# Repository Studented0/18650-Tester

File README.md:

# CellScan
 
A 4-channel 18650 battery analyzer. Tests up to 4 cells at once and measures voltage, capacity in mAh, and internal resistance per channel. Results show on a small OLED with a rotary encoder to navigate, and a WiFi dashboard to start and stop tests remotely/edit settings.
 
---
 
## Screenshots

---
 
## Why I built this
 
My science fair project was a 3S34P battery pack from 34 salvaged 18650 cells. I bought a cheap tester off Amazon to sort them but I wanted to know how it actually worked. I also wanted an excuse to learn PCB design. CellScan is the result, a two-layer PCB with SMD assembly through JLCPCB.
 
---
 
## Hardware
 
Two-layer board, 100×150mm, designed in KiCad 9. SMD components assembled by JLCPCB. Through-hole parts soldered by hand after the board arrives: four MOSFETs, four cement resistors, four cell holders, the OLED header, the ESP32 dev board, and the rotary encoder. The cement resistors run hot under load so they sit raised slightly off the board.
 
Each channel has an INA219 current sensor, an IRLZ44N MOSFET as a discharge switch, and a 1Ω 10W cement resistor as the load. All four INA219s share an I2C bus through a TCA9548A multiplexer since they would otherwise have the same address. Each channel also has a TP4056 lithium charger for charging and discharging. 
 
---
 
## How it measures
 
**Voltage** — INA219 reads bus voltage continuously on each channel.
 
**Capacity** — ESP32 switches the MOSFET on to start discharge. Capacity accumulates by coulomb counting every 500ms until the cell hits the cutoff voltage.
 
`mAh += current_mA * (elapsed_ms / 3600000.0)`
 
**Internal resistance (DCIR)** — Measured at test start using voltage sag. MOSFET off, read open-circuit voltage. MOSFET on, wait 100ms, read loaded voltage and current.
 
`ESR (mΩ) = (V_oc - V_load) / I_load * 1000`
 
---
 
## Rotary Encoder
 
EC11 encoder wired directly to the ESP32. Rotate to switch between channels, press to open a menu, long press to go back. From the menu you can start a test, stop it, or adjust the cutoff voltage per channel. 
 
### Wiring
 
| Signal | GPIO |
|--------|------|
| ENC_A | 15 |
| ENC_B | 2 |
| ENC_SW | 5 |
| SDA | 21 |
| SCL | 22 |
 
---
 
## Firmware
 
`firmware/CellScan.ino` — state machine per channel, coulomb counting, DCIR measurement, TP4056 CE control, rotary encoder UI, OLED display, WiFi dashboard.
 
Libraries needed: Adafruit INA219, Adafruit SSD1306, Adafruit GFX, ArduinoJson. Install through Arduino IDE library manager. Board: ESP32 Dev Module.
 
---
 
## Bill of Materials
 
SMD parts ordered through JLCPCB assembly. Through-hole parts sourced separately.
 
| Component | Qty | LCSC | Note |
|-----------|-----|------|------|
| 100nF 0402 cap | 11 | C1525 | Basic |
| 10kΩ 0402 resistor | 7 | C25744 | Basic |
| 5.1kΩ 0402 resistor | 2 | C25905 | Basic — USB-C CC pull-downs |
| 1.2kΩ 0402 resistor | 4 | C25862 | Extended — TP4056 PROG |
| 1kΩ 0402 resistor | 8 | C11702 | Basic — LED series |
| Red LED 0402 | 8 | C71911 | Extended |
| INA219AIDR | 4 | C138706 | Extended |
| TCA9548AMRGER | 1 | C2876717 | Extended |
| TP4056 SOP-8 | 4 | C16581 | Extended |
| GCT USB4125 USB-C | 1 | C2682777 | Extended |
 
| Component | Qty | Link |
|-----------|-----|------|
| ESP32 WROOM-32 dev board | 1 | [Amazon](https://www.amazon.com/dp/B08D5ZD528) |
| IRLZ44N MOSFET | 4 | [Amazon](https://www.amazon.com/Technologies-Threshold-Protective-Packaging-IRLZ44NPBF/dp/B0FMQCYG6Q/) |
| 1Ω 10W cement resistor | 4 | [Amazon](https://www.amazon.com/Resistors-Wirewound-Resistance-Precharge-Horizontal/dp/B09V5MTX8Q/) |
| 18650 cell holders | 4 | [Amazon](https://www.amazon.com/Battery-Storage-Holder-Button-Single/dp/B07KD9JLH3/) |
| SSD1306 OLED 0.96" | 1 | [Amazon](https://www.amazon.com/UCTRONICS-SSD1306-Self-Luminous-Display-Raspberry/dp/B072Q2X2LL/) |
| EC11 rotary encoder | 1 | already owned |
 
---
 
## Repository Structure
 
```
18650-Tester/
├── BOM.csv
├── README.md
├── firmware/
│   └── CellScan.ino
└── hardware/
    ├── CellScan_Schematic.kicad_sch
    ├── CellScan_Schematic.kicad_pcb
    ├── CellScan_Schematic.kicad_pro
    ├── CellScan_Schematic.pdf
    ├── libraries/
    │   └── ESP32-DevKitC-30PIN.kicad_mod
    └── gerbers/
```
 
---
 
## License
 
[MIT](LICENSE)

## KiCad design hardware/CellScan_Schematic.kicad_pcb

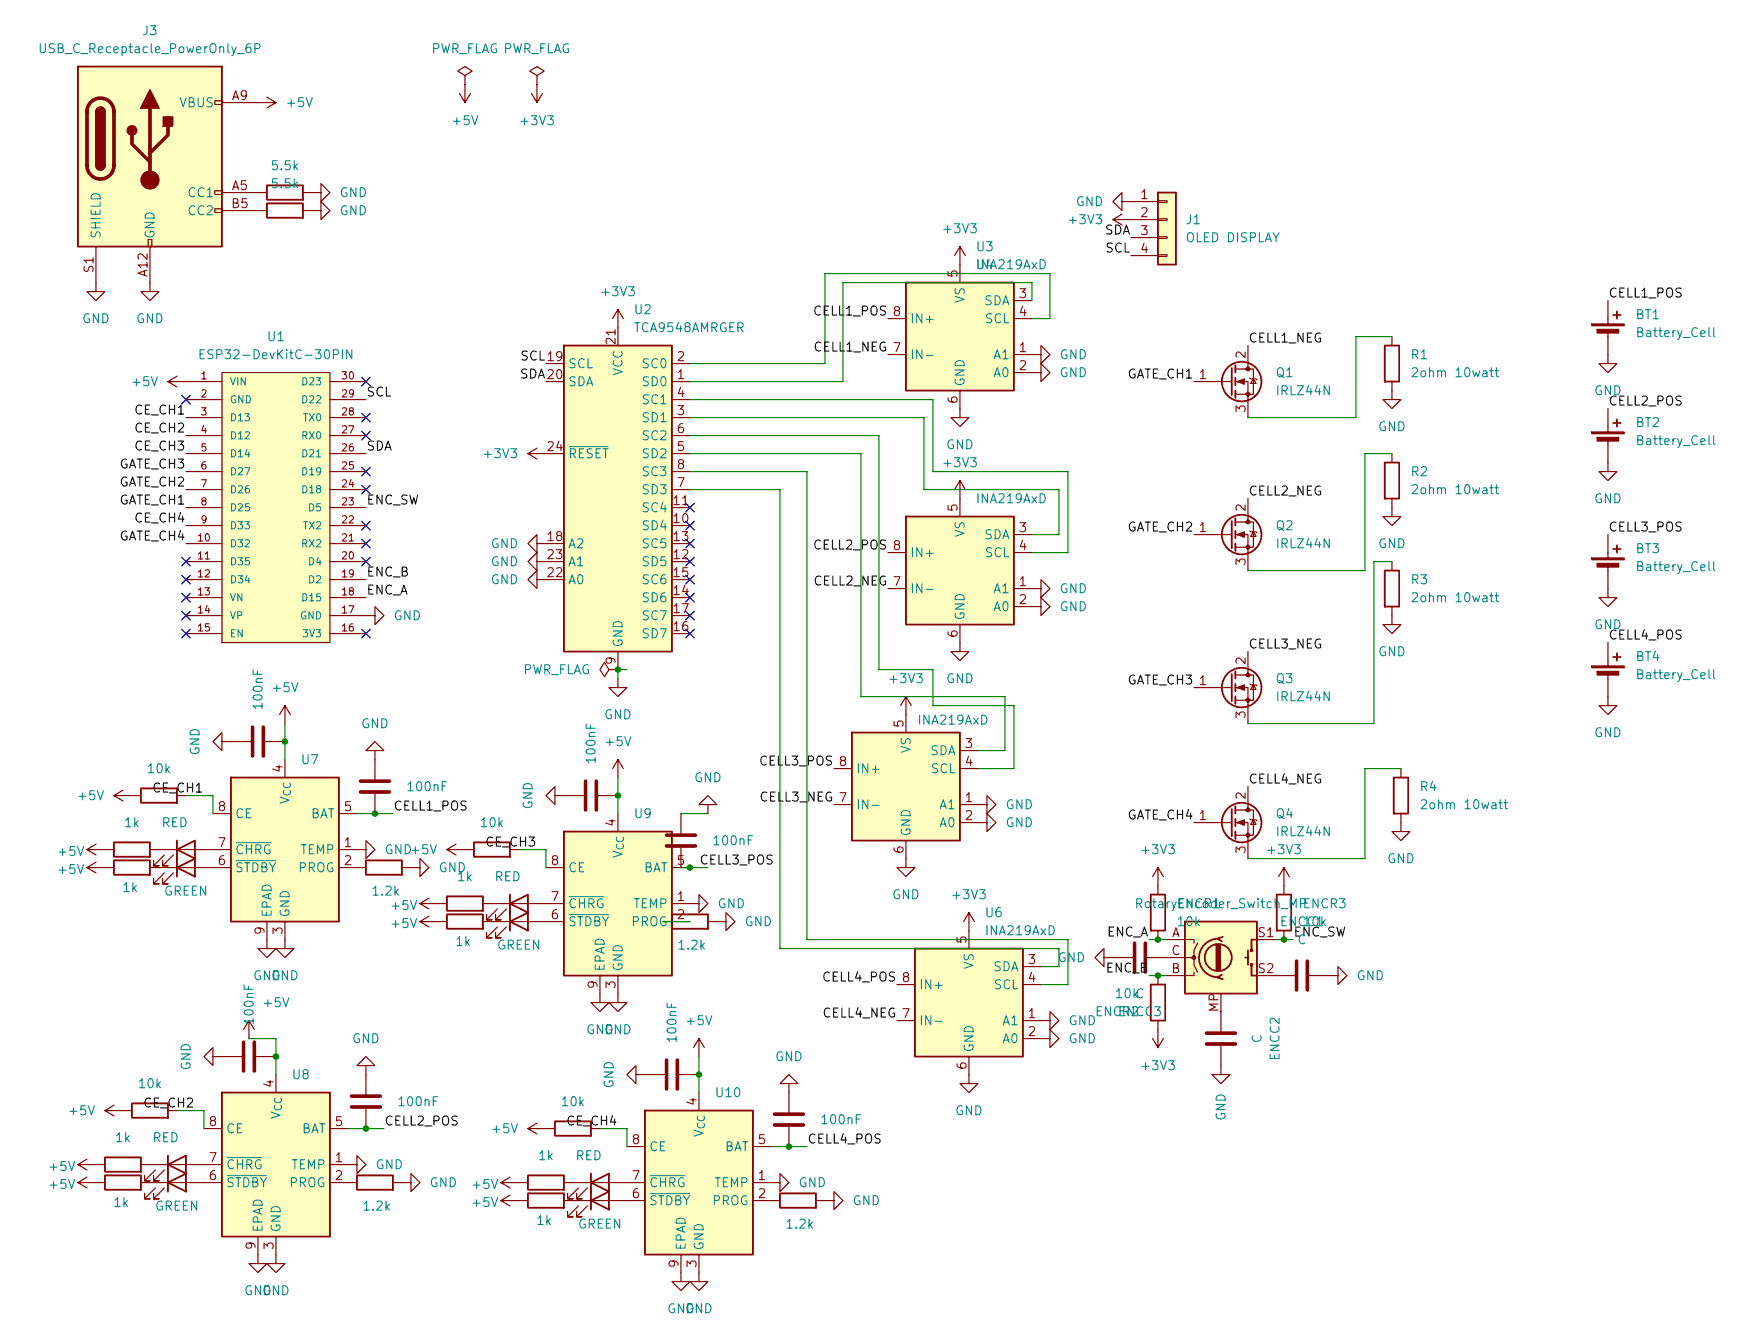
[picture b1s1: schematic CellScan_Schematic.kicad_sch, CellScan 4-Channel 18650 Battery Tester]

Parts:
BAT1.1, BAT2.1, BAT3.1, BAT4.1: 10k; R_0402_1005Metric
BAT1.2, BAT2.2, BAT3.2, BAT4.2: 1.2k; R_0402_1005Metric
BAT1.3, BAT1.4, BAT2.3, BAT2.4, BAT3.3, BAT3.4, BAT4.3, BAT4.4: 100nF; C_0402_1005Metric
BAT1GREEN1, BAT1RED1, BAT2GREEN1, BAT2RED1, BAT3GREEN1, BAT3RED1, BAT4GREEN1, BAT4RED1: 1k; LED_0402_1005Metric
BT1, BT2, BT3, BT4: Battery_Cell; BatteryHolder_Keystone_1042_1x18650
ENCC1, ENCC2, ENCC3: C; C_0402_1005Metric
ENCR1, ENCR2, ENCR3: 10k; R_0402_1005Metric
GREEN1, GREEN2, GREEN3, GREEN4: GREEN; LED_0402_1005Metric
J1: OLED DISPLAY; PinHeader_1x04_P2.54mm_Vertical
J3: USB_C_Receptacle_PowerOnly_6P; USB_C_Receptacle_GCT_USB4125-xx-x-0190_6P_TopMnt_Horizontal
Q1, Q2, Q3, Q4: IRLZ44N; TO-220-3_Vertical
R1, R2, R3, R4: 2ohm 10watt; R_Axial_Power_L48.0mm_W12.5mm_P55.88mm
R5, R6: 5.5k; R_0402_1005Metric
RED1, RED2, RED3, RED4: RED; LED_0402_1005Metric
SW1: RotaryEncoder_Switch_MP; RotaryEncoder_Alps_EC11E-Switch_Vertical_H20mm
U1: ESP32-DevKitC-30PIN
U2: TCA9548AMRGER; Texas_RGE0024C_VQFN-24-1EP_4x4mm_P0.5mm_EP2.1x2.1mm
U3, U4, U5, U6: INA219AxD; SOIC-8_3.9x4.9mm_P1.27mm
U7, U8, U9, U10: TP4056-42-ESOP8; SOIC-8-1EP_3.9x4.9mm_P1.27mm_EP2.41x3.3mm_ThermalVias

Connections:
+3V3: ENCR1.1, ENCR2.1, ENCR3.1, J1.2, U2.21 (VCC), U2.24 (~RESET), U3.5 (VS), U4.5 (VS), U5.5 (VS), U6.5 (VS)
+5V: BAT1.1.1, BAT1.4.2, BAT1GREEN1.1, BAT1RED1.1, BAT2.1.1, BAT2.4.2, BAT2GREEN1.1, BAT2RED1.1, BAT3.1.1, BAT3.4.2, BAT3GREEN1.1, BAT3RED1.1, BAT4.1.1, BAT4.4.2, BAT4GREEN1.1, BAT4RED1.1, J3.A9 (VBUS), J3.B9 (VBUS), U1.1 (VIN), U7.4 (V_{CC}), U8.4 (V_{CC}), U9.4 (V_{CC}), U10.4 (V_{CC})
/CELL1_NEG: Q1.2 (D), U3.7 (IN-)
/CELL1_POS: BAT1.3.2, BT1.1 (+), U3.8 (IN+), U7.5 (BAT)
/CELL2_NEG: Q2.2 (D), U4.7 (IN-)
/CELL2_POS: BAT2.3.2, BT2.1 (+), U4.8 (IN+), U8.5 (BAT)
/CELL3_NEG: Q3.2 (D), U5.7 (IN-)
/CELL3_POS: BAT4.3.2, BT3.1 (+), U5.8 (IN+), U9.5 (BAT)
/CELL4_NEG: Q4.2 (D), U6.7 (IN-)
/CELL4_POS: BAT3.3.2, BT4.1 (+), U6.8 (IN+), U10.5 (BAT)
/CE_CH1: BAT1.1.2, U1.3 (D13), U7.8 (CE)
/CE_CH2: BAT2.1.2, U1.4 (D12), U8.8 (CE)
/CE_CH3: BAT4.1.2, U1.5 (D14), U9.8 (CE)
/CE_CH4: BAT3.1.2, U1.9 (D33), U10.8 (CE)
/ENC_A: ENCR1.2, SW1.A, U1.18 (D15)
/ENC_B: ENCR2.2, SW1.B, U1.19 (D2)
/ENC_SW: ENCR3.2, SW1.S1, U1.23 (D5)
/GATE_CH1: Q1.1 (G), U1.8 (D25)
/GATE_CH2: Q2.1 (G), U1.7 (D26)
/GATE_CH3: Q3.1 (G), U1.6 (D27)
/GATE_CH4: Q4.1 (G), U1.10 (D32)
/SCL: J1.4, U1.29 (D22), U2.19 (SCL)
/SDA: J1.3, U1.26 (D21), U2.20 (SDA)
GND: BAT1.2.2, BAT1.3.1, BAT1.4.1, BAT2.2.2, BAT2.3.1, BAT2.4.1, BAT3.2.2, BAT3.3.1, BAT3.4.1, BAT4.2.2, BAT4.3.1, BAT4.4.1, BT1.2 (-), BT2.2 (-), BT3.2 (-), BT4.2 (-), ENCC1.2, ENCC2.2, ENCC3.2, J1.1, J3.A12 (GND), J3.B12 (GND), J3.S1 (SHIELD), R1.2, R2.2, R3.2, R4.2, R5.2, R6.2, U1.17 (GND), U2.9 (GND), U2.18 (A2), U2.22 (A0), U2.23 (A1), U3.1 (A1), U3.2 (A0), U3.6 (GND), U4.1 (A1), U4.2 (A0), U4.6 (GND), U5.1 (A1), U5.2 (A0), U5.6 (GND), U6.1 (A1), U6.2 (A0), U6.6 (GND), U7.1 (TEMP), U7.3 (GND), U7.9 (EPAD), U8.1 (TEMP), U8.3 (GND), U8.9 (EPAD), U9.1 (TEMP), U9.3 (GND), U9.9 (EPAD), U10.1 (TEMP), U10.3 (GND), U10.9 (EPAD)
unnamed: ENCC1.1, SW1.S2
unnamed: ENCC2.1, SW1.MP
unnamed: ENCC3.1, SW1.C
unnamed: GREEN1.2 (A), U7.6 (~STDBY)
unnamed: BAT1GREEN1.2, GREEN1.1 (K)
unnamed: GREEN2.2 (A), U8.6 (~STDBY)
unnamed: BAT2GREEN1.2, GREEN2.1 (K)
unnamed: GREEN3.2 (A), U9.6 (~STDBY)
unnamed: BAT4RED1.2, GREEN3.1 (K)
unnamed: GREEN4.2 (A), U10.6 (~STDBY)
unnamed: BAT3GREEN1.2, GREEN4.1 (K)
unnamed: J3.A5 (CC1), R5.1
unnamed: J3.B5 (CC2), R6.1
unnamed: Q1.3 (S), R1.1
unnamed: Q2.3 (S), R2.1
unnamed: Q3.3 (S), R3.1
unnamed: Q4.3 (S), R4.1
unnamed: RED1.2 (A), U7.7 (~CHRG)
unnamed: BAT1RED1.2, RED1.1 (K)
unnamed: RED2.2 (A), U8.7 (~CHRG)
unnamed: BAT2RED1.2, RED2.1 (K)
unnamed: RED3.2 (A), U9.7 (~CHRG)
unnamed: BAT4GREEN1.2, RED3.1 (K)
unnamed: RED4.2 (A), U10.7 (~CHRG)
unnamed: BAT3RED1.2, RED4.1 (K)
unnamed: U2.2 (SC0), U3.4 (SCL)
unnamed: U2.4 (SC1), U4.4 (SCL)
unnamed: U2.6 (SC2), U5.4 (SCL)
unnamed: U2.8 (SC3), U6.4 (SCL)
unnamed: U2.1 (SD0), U3.3 (SDA)
unnamed: U2.3 (SD1), U4.3 (SDA)
unnamed: U2.5 (SD2), U5.3 (SDA)
unnamed: U2.7 (SD3), U6.3 (SDA)
unnamed: BAT1.2.1, U7.2 (PROG)
unnamed: BAT2.2.1, U8.2 (PROG)
unnamed: BAT4.2.1, U9.2 (PROG)
unnamed: BAT3.2.1, U10.2 (PROG)

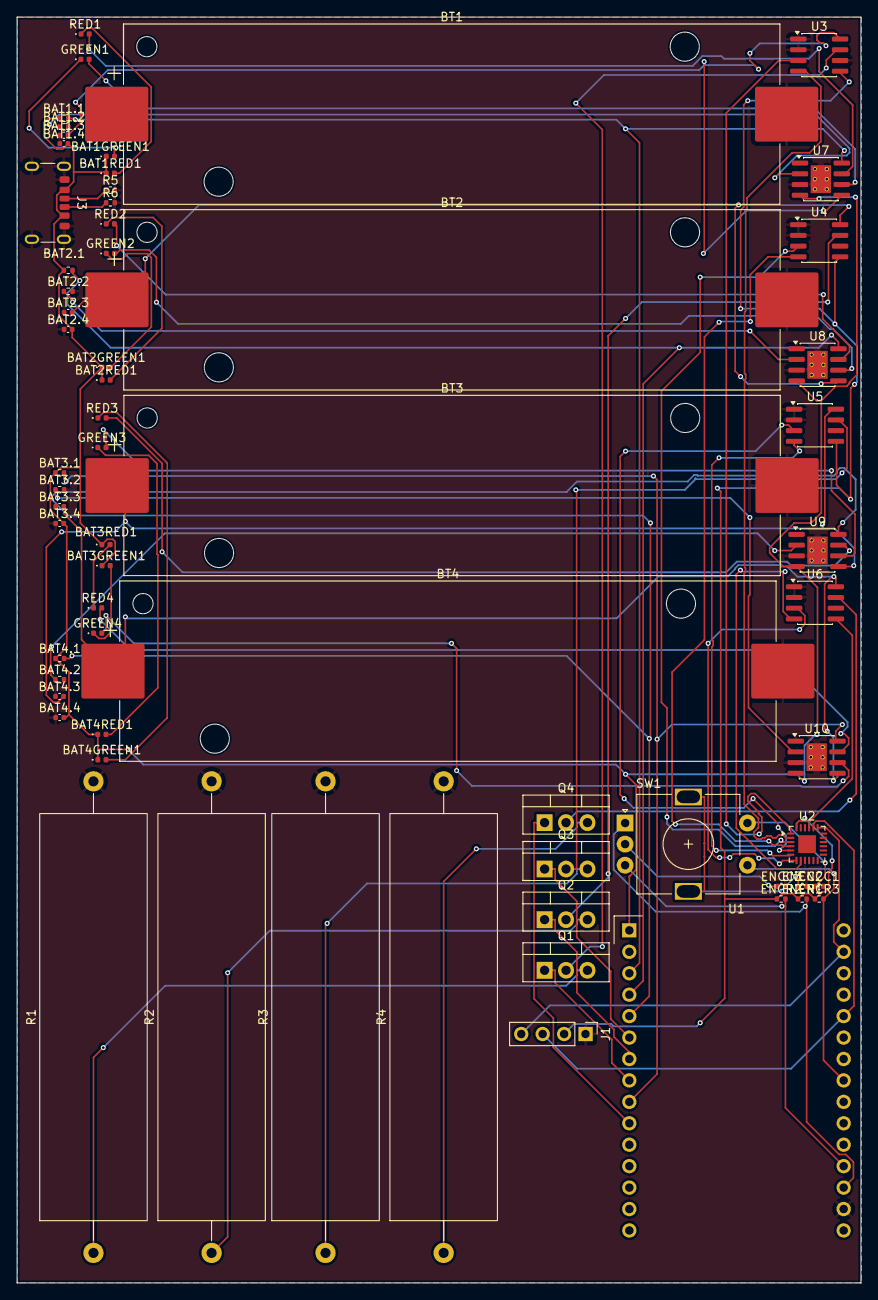
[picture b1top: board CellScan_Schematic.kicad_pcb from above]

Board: 2 copper layers, 100.0 x 150.0 mm, 65 parts (0 on the bottom side), 61 nets.

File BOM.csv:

Comment,Designator,Footprint,Quantity,LCSC Part,Note
100nF,BAT1.3 BAT1.4 BAT2.3 BAT2.4 BAT3.3 BAT3.4 BAT4.3 BAT4.4 ENCC1 ENCC2 ENCC3,C_0402_1005Metric,11,C1525,Basic
10k,BAT1.1 BAT2.1 BAT3.1 BAT4.1 ENCR1 ENCR2 ENCR3,R_0402_1005Metric,7,C25744,Basic
5.1k,R5 R6,R_0402_1005Metric,2,C25905,Basic — CC1/CC2 USB-C pull-downs
1.2k,BAT1.2 BAT2.2 BAT3.2 BAT4.2,R_0402_1005Metric,4,C25862,Extended — TP4056 PROG resistors
1k,BAT1RED1 BAT1GREEN1 BAT2RED1 BAT2GREEN1 BAT3RED1 BAT3GREEN1 BAT4RED1 BAT4GREEN1,R_0402_1005Metric,8,C11702,Basic — LED series resistors
RED LED 0402,RED1 RED2 RED3 RED4 GREEN1 GREEN2 GREEN3 GREEN4,LED_0402_1005Metric,8,C71911,Extended — all indicators use same red LED
INA219AIDR,U3 U4 U5 U6,SOIC-8_3.9x4.9mm_P1.27mm,4,C138706,Extended
TCA9548AMRGER,U2,Texas_RGE0024C_VQFN-24-1EP_4x4mm_P0.5mm_EP2.1x2.1mm,1,C2876717,Extended
TP4056-42-ESOP8,U7 U8 U9 U10,SOIC-8-1EP_3.9x4.9mm_P1.27mm_EP2.41x3.3mm_ThermalVias,4,C16581,Extended
GCT USB4125 USB-C,J3,USB_C_Receptacle_GCT_USB4125,1,C2682777,Extended — dedicated 5V power input

-- THROUGH-HOLE (manual solder) --
IRLZ44N MOSFET,Q1 Q2 Q3 Q4,TO-220-3_Vertical,4,,Amazon — solder by hand
1ohm 10W resistor,R1 R2 R3 R4,R_Axial_Power_L48.0mm_W12.5mm_P55.88mm,4,,Amazon — solder by hand
18650 cell holder,BT1 BT2 BT3 BT4,BatteryHolder_Keystone_1042_1x18650,4,,Amazon — solder by hand
OLED 4-pin header,J1,PinHeader_1x04_P2.54mm_Vertical,1,,Amazon — solder by hand
ESP32-WROOM-32 dev board,U1,ESP32-DevKitC-30PIN,1,,Amazon — socket or solder by hand
EC11 rotary encoder,SW1,RotaryEncoder_Alps_EC11E-Switch_Vertical_H20mm,1,,JLCPCB PCB — solder by hand

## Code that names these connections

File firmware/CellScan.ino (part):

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 *
 * Pin map:
 *   SDA       = GPIO21   SCL       = GPIO22
 *   GATE_CH1  = GPIO25   GATE_CH2  = GPIO26
 *   GATE_CH3  = GPIO27   GATE_CH4  = GPIO32
 *   CE_CH1    = GPIO13   CE_CH2    = GPIO12  (see boot note below)
 *   CE_CH3    = GPIO14   CE_CH4    = GPIO33
 *   ENC_A     = GPIO15   ENC_B     = GPIO2   ENC_SW = GPIO5
 *
 * HARDWARE NOTE — GPIO12 (CE_CH2):
 *   GPIO12 is a strapping pin. High at boot selects 1.8V flash mode,
 *   which causes boot failures on standard 3.3V flash modules.
 *   Burn EFLASH if needed
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const int MOSFET_PINS[NUM_CH] = {25, 26, 27, 32};
const int CE_PINS[NUM_CH]     = {13, 12, 14, 33};

#define ENC_A   15
#define ENC_B   2
#define ENC_SW  5

#define CUTOFF_DEF   2.80f
#define CUTOFF_MIN   2.50f
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    ce_on(i);
  }

  pinMode(ENC_A,  INPUT);
  pinMode(ENC_B,  INPUT);
  pinMode(ENC_SW, INPUT);
  attachInterrupt(digitalPinToInterrupt(ENC_A), enc_isr, RISING);

  Wire.begin(21, 22);
  tca(0);
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
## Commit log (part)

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2026-03-04 Create temp
2026-03-04 Create tewst
2026-03-04 Create test
2026-03-05 Revise README for CellScan 18650 Battery Analyzer
    Updated project name and expanded README with detailed features, measurements, wiring diagram, bill of materials, firmware details, and repository structure.
2026-03-05 Add files via upload
    unfinished version of main schematic
2026-03-05 Revise Bill of Materials and update total cost
    Updated bill of materials and total cost.
2026-04-14 Add firmware
2026-04-14 Revise README content and fix links
    Updated descriptions and links in the README file for clarity and accuracy.
2026-04-14 Add MIT License to the project
2026-04-14 Fix schematic link in README
    Updated the link for the CellScan schematic in the README.
2026-04-26 Updated Firmware for PCB
2026-04-26 Gerber files and BOM and whatnot
2026-04-26 Revise README for clarity and additional details
    Updated project description, system architecture, and wiring diagram. Enhanced explanations for measurements and added details about firmware and assembly.
2026-04-26 Update README with assembly images and details
    Added images to the README for assembly and hardware details.
2026-04-28 Revise README for clarity and additional details
    Updated the README to improve clarity and structure, added screenshots, and refined technical details.
